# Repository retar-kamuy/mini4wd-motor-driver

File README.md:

# Mini 4WD Motor Driver 開発版

[keimyojizai/mini4wd-motor-driver](https://github.com/keimyojizai/mini4wd-motor-driver) を元に開発している [retar-kamuy のフォーク](https://github.com/retar-kamuy/mini4wd-motor-driver) です。

**販売・量産を目的としない個人の趣味用試作です。基板上の全SMT部品を業者へ実装委託して完成させる設計で、手はんだ後付けを前提にしません。発注枚数は固定せず、故障時の交換や予備を含む複数枚注文を想定します。現在の設計は検証中で、発注に使える状態ではありません。** 正規設計は37部品を全てF.Cu側に配置し、記録済み版ではERC・DRC・未接続・回路図不一致は0件、116パッドのネット照合も一致しました。搭載性は一般的な実現性を評価し、個々のシャーシやカウルへの適合は保証しません。フロントモーターのFM-A/SFMは対象外です。部品・ランド、PCBA用BOM/CPL、業者のファイル・組立条件確認が残っています。完成基板の電流・温度・過渡波形は試作後に確認します。品質基準と現版の変更は[趣味用途の品質レビュー](specs/003-resolve-pcb-drc/verification/hobby-quality-review.md)および[試作版の反映記録](specs/003-resolve-pcb-drc/verification/prototype-design-release.md)を参照してください。

**対応電池の設計要件：単3形NiMH充電池2本／単3形アルカリ乾電池2本の両方。** 両電池に対応する方針で電源・駆動回路を設計しています。対応電圧範囲、起動・低電圧時の動作、モーター負荷および実機動作は検証中です。現時点で両電池での動作確認完了を示すものではありません。

**対応モーターの設計意図：型番で限定しないこと。** 代表負荷と保護範囲を確認します。電池との組合せによる起動・ストール・ブレーキ時の過渡電流と保護の検討は未完了で、未知の全モーターの動作保証を意味しません。

| 内容 | 正本・入口 |
|---|---|
| 現行KiCad設計 | [hardware/kicad/mini4wd-motor-driver](hardware/kicad/mini4wd-motor-driver/) |
| 基板の残課題 | [specs/003-resolve-pcb-drc/tasks.md](specs/003-resolve-pcb-drc/tasks.md) |
| ファームウェア | [firmware/mini4ai_v358](firmware/mini4ai_v358/) |
| Webアプリ | [web/index.html](web/index.html) |
| 利用資料 | [docs](docs/) |
| 開発環境 | [SETUP.md](SETUP.md) |
| 構成と来歴 | [docs/repository_structure.md](docs/repository_structure.md) |

以下は元プロジェクトを基にした利用案内です。掲載された既存基板の写真・動作説明は、開発中のKiCad基板の製造承認を意味しません。

---

# ミニ四駆AI モータードライバ基板

**XIAO MG24 Sense専用 / 正転専用 / ショートブレーキ対応 MOSFETドライバ**

ミニ四駆に電子制御を追加するための、  
**XIAO MG24 Sense専用 高電流モータードライバ基板**です。

- **Nch MOSFETによるモーター駆動**
- **Pch MOSFETによるショートブレーキ**
- **1本のPWM信号で駆動 / 制動を切り替え**
- **発進時のソフトスタートに対応**
- **電池電圧・M-側電圧・基板温度の観測に対応**
- **Ni-MH 2セル / Li-ion 1セル向け**

> 本基板は、改造・競技・研究・教育用途を想定した電子工作向け部品です。  
> はんだ付け、配線、電源極性、モーター制御に関する基礎知識が必要です。

---

## 購入後に使用するもの

本基板を使用するには、XIAO MG24 Senseへ専用ファームウェアを書き込み、WebアプリからBLE接続して設定・走行制御を行います。

- [Webアプリを開く](https://keimyojizai.github.io/mini4wd-motor-driver/)
- [Windows書き込みツールをダウンロード](https://github.com/keimyojizai/mini4wd-motor-driver/releases/latest)
- [ファームウェア更新手順](docs/firmware_update.md)
- [本体へ保存とスタンドアローン起動](docs/standalone_mode.md)
- [Arduino IDEで手動書き込みする手順](docs/flash_arduino_ide.md)
- [書き込みに失敗した場合の復旧手順](docs/recovery.md)

### Webアプリでできること

- デバイスへのBLE接続
- 走行開始・停止
- 認識調整
- ルール設定
- かんたん設定で、90度/180度/それ以上のカーブ継続を別々に選択
- 別画面のかんたん設定ウィザード（1画面1判断）
- かんたん設定内で2つ目・3つ目のルールを追加可能
- かんたん設定中は専用ルールセットだけを走行に反映し、過去ルールとの重複発火を防止
- 目的位置の手前を起点にした時間差アクション設定
- 電圧補正設定
- ラップタイム確認
- 停止後ログ確認
- ヘッダー非表示による走行・ラップ表示の拡大
- ファームウェアバージョン確認
- BLE表示名の変更
- 現在の設定を本体へ保存
- 保存済み設定によるスタンドアローン起動

### 初回ファームウェア書き込み

初回使用時、またはファームウェア更新時は、Windows用書き込みツールを使用してください。

1. GitHub ReleasesからWindows用書き込みツールをダウンロードします。
2. ZIPを右クリックして「すべて展開」します。
3. 展開したフォルダ内の `START_HERE_Flash_Mini4AI.cmd` を実行します。
4. 書き込み時に、BLE表示名を自由に設定できます。

> ファームウェア書き込み時は、**ミニ四駆側の電源をオフ** にしてからUSB接続してください。

macOS / Linux用の書き込みツールは、現時点では動作確認対象外のため同梱していません。Windows用書き込みツールでうまくいかない場合や、他OSで使用する場合はArduino IDEで手動書き込みしてください。

### 本体へ保存とスタンドアローン起動

Webアプリで設定した内容には、**一時適用**と**本体へ保存**があります。

- **走行開始**: 現在の画面設定を一時的に本体へ送信して走行します。電源を切ると、この一時設定は残りません。
- **本体へ保存**: 現在のパラメータ、ルール、電圧補正、周回認識設定をXIAO MG24 Sense本体へ保存します。
- **スタンドアローン起動**: 保存済み設定がある状態で、裏返しのまま電源ON → 表向きに戻す → 約3秒後にBLEなしで自動スタートします。

スタンドアローン起動で使いたい設定は、必ずWebアプリ左メニューの **「本体へ保存」** を押してから使用してください。

Webアプリでは、誤操作を避けるため「走行開始」「停止」とは離した左メニューに **本体へ保存** を配置しています。保存時には確認画面で「はい / いいえ」を選択します。

詳細は [本体へ保存とスタンドアローン起動](docs/standalone_mode.md) を参照してください。

### かんたん設定モード

Webアプリには、通常の詳細UIとは別に、1画面1判断で進む **かんたん設定** があります。
目的位置、起点セクション、発動回数、待機時間、ブレーキ/低出力を順番に設定できます。

走行後に「早すぎた」「遅すぎた」「発動しなかった」「違う場所でも発動した」を選ぶと、修正すべき画面へ戻ります。
このとき、改善アドバイスを画面上部に表示し続けるため、何を直すべきか確認しながら調整できます。

1つ目のルールが決まった後も、かんたん設定のまま2つ目・3つ目のルールを追加できます。

### 推奨バージョン

| 項目 | 推奨バージョン |
|---|---|
| Webアプリ | v4.21-r33 |

かんたん設定では単発の左C/右Cを初期状態で非表示にし、誤発動しにくい左/右カーブ継続を基本にしています。
| ファームウェア | v3.58-r10 |

Webアプリ上で、接続中デバイスのファームウェアバージョンを確認できます。

---

## 外観・パッケージ・装着例

### 基板単体

### 販売パッケージ

### ミニ四駆への装着例

> 装着例です。ミニ四駆車体、XIAO MG24 Sense、モーター、電池、配線材等は付属しません。

### 動作例

[YouTube Shortsで動作例を見る](https://youtube.com/shorts/a6D7kiM3N_Y?feature=share)

---

## どのような基板か

本基板は、ミニ四駆で一般的な

```text
M+ / B+ = 電池＋ / モーター＋ 共通
M-      = モーター−
B-      = 電池−
```

という構成を前提にした、**正転専用・M-側制御**のモータードライバです。

Hブリッジではなく、機能を

- **正転駆動**
- **ショートブレーキ**
- **各種センシング**

に絞ることで、ミニ四駆AI制御向けに小型化と高電流駆動を狙っています。

---

## 主な特徴

- **XIAO MG24 Sense専用設計**
- **正転専用**。逆転制御には非対応
- **Nch MOSFETによる低側駆動**
- **Pch MOSFETによるショートブレーキ**
- **UCC27511による5Vゲート駆動**
- **TPS61023による5V昇圧電源**
- **XIAO MG24 Senseへの5V給電**
- **VBAT / MID / 温度の観測に対応**
- **発進時のソフトスタートに対応**
- **DRV8835系ドライバでは駆動できなかったモーターの駆動を手元評価で確認**

---

## ソフトウェア制御について

本基板は、XIAO MG24 Sense上のファームウェアでモーターを制御します。

- 走行開始時は、設定されたDutyへ一気に上げず、短時間のソフトスタートを行います。
- 走行中のルール判定、ブレーキ、低出力制御は本体側で実行されます。
- Webアプリは、設定・開始/停止指示・ログ確認を行うための操作画面です。
- Webアプリの走行開始は、現在の画面設定を一時適用します。
- スタンドアローン起動で使う設定は、Webアプリの **「本体へ保存」** を押したときだけ更新されます。
- BLE接続が切れても、走行中の制御判断は本体側で継続します。

## ルール設計の基本

目的の場所で止める、または減速する場合は、**その場所そのものを認識してからブレーキするのではなく、手前の特徴的なセクションを起点にして時間差でアクション**します。

例として、ウェーブで止まりたい場合、ウェーブを認識してからブレーキすると遅れることがあります。ウェーブの手前にある特徴的なセクションを起点にし、待機msで位置を合わせてからブレーキ/低出力を出します。

最初は1〜2セグメントの短い条件で作り、同じ起点が複数回出る場合は、奇数回・偶数回・N回のみの発動条件を使います。

Webアプリの **かんたん設定** は通常画面とは別画面で開き、1画面につき1つの判断だけを表示します。
最後の接続前には、設定したルールを自然文で確認できます。
走行後は「発動しない」「早すぎる」「遅すぎる」「余計な場所でも出る」から選ぶと、次に触るべき設定を1つに絞って提案します。

詳細は [かんたん設定ウィザード](docs/guided_setup.md) を参照してください。

---

## 重要な注意事項

使用前に必ず確認してください。

```text
・XIAO MG24 Sense専用です
・XIAO MG24 Senseは付属しません
・正転専用です
・逆転制御はできません
・Hブリッジではありません
・PWM Duty 0%ではショートブレーキになります
・電池の逆接続は禁止です
・Li-ion 2セルは禁止です
・8.4V系電源は禁止です
・FM-A / SFMシャーシには基本的に非対応です
・フェンスカー等の電池逆向き運用には、そのまま使用できません
・ファームウェア書き込み時は、ミニ四駆側の電源をオフにしてからUSB接続してください
```

---

## 基本仕様

| 項目 | 内容 |
|---|---|
| 対応マイコン | XIAO MG24 Sense専用 |
| 駆動方式 | 正転専用、M-側制御 |
| モーター制御 | Nch MOSFET低側駆動 |
| ブレーキ | Pch MOSFETによるショートブレーキ |
| 制御信号 | PWM入力 1本 |
| 想定電源 | Ni-MH 2セル / Li-ion 1セル |
| 非対応電源 | Li-ion 2セル、8.4V系電源 |
| 基板サイズ | 約 55 mm × 21 mm |
| 基板厚 | 1.2 mm |

---

## 接続概要

### 大電流端子

```text
M+ / B+ = 電池＋ / モーター＋ 共通
M-      = モーター−
B-      = 電池−
```

### XIAO MG24 Senseとのピン対応

| XIAO MG24 Sense | 本基板での機能 |
|---|---|
| 5V | 5V OUT |
| GND | GND |
| PC0（D0） | VBAT SENSE |
| PC1（D1） | NTC TEMP |
| PC2（D2） | MOTOR PWM |
| PC3（D3） | MID SENSE |

---

## 詳細ドキュメント

READMEでは概要のみを示しています。  
設計意図・配線・動作原理・注意事項の詳細は、以下を参照してください。

- [ファームウェア更新手順](docs/firmware_update.md)
- [本体へ保存とスタンドアローン起動](docs/standalone_mode.md)
- [Arduino IDEで手動書き込みする手順](docs/flash_arduino_ide.md)
- [書き込みに失敗した場合の復旧手順](docs/recovery.md)
- [トラブルシュート](docs/troubleshooting.md)
- [かんたん設定ウィザード](docs/guided_setup.md)
- [ハードウェア仕様と主要部品](docs/hardware_spec.md)
- [配線・取り付け・対応シャーシ](docs/wiring_and_usage.md)
- [PWM制御とショートブレーキの動作](docs/pwm_and_brake.md)
- [安全上の注意・免責事項・サポート](docs/safety_and_support.md)

---

## サポート

不具合報告・質問・改善提案は、GitHubの **Issues** を使用してください。  
問い合わせ時は、以下の情報を記載してください。

- 使用しているWebアプリのバージョン
- 使用しているファームウェアのバージョン
- XIAO MG24 SenseのBLE表示名
- 使用電源
- 使用モーター
- 症状が起きた操作手順
- 可能であれば、Webアプリの停止後ログ

---

## 商標について

- ミニ四駆は株式会社タミヤの登録商標です。
- 本基板は株式会社タミヤの公式製品・公認製品ではありません。
- 本基板は個人開発の改造・実験用基板です。

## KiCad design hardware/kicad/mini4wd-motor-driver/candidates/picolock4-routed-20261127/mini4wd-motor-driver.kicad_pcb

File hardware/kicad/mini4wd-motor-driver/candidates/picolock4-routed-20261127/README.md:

# 004 Pico-Lock 4極・配線候補

2026-11-27。4極コネクタ案の別候補。004正規版と元の `picolock4-20261126` は変更していない。J1を右へ5 mm移動、右端を5.5 mm延長し、外形は60.5 × 21 mmとなった。元の55 × 21 mmに対する車体収納は未確認。

J1のピン1=MOTOR_MINUS、2=VBAT（モーター＋）、3=GND（電池−）、4=VBAT（電池＋）。電池とモーターを1つにまとめる専用ハーネスが必要。極性を回路図とメーカー図面で再確認する。旧配置のB+/B−/M+/M−シルクはF.Fabに移動し、ピンの位置に対応する新しい表示を表面シルクへ追加した。J1の基板端からはみ出すシルク外形もF.Fabへ移した。

旧候補のJ1付近の配線を整理し、自動配線で再接続した。新規配線はVBAT/MOTOR_MINUS/GNDに1.0 mmの指定を与えたが、電流経路には既存の細線やビアも含まれる。1.0 mm指定やDRC合格は5 A連続の許容を意味せず、電流分流、銅厚、ビア、発熱は未評価。メーカーの4極AWG20参考値は5.5 A/極で、始動・拘束の適否も未確定。[Molex仕様](https://www.molex.com/content/dam/molex/molex-dot-com/en_us/pdf/datasheets/987650-9061.pdf)

2026-11-28、J1の電池マイナスから裏面GND面への接続が1本のビアに集中していたため、元の1本に加え穴径0.3 mmのビアを3本並列に追加した。追加後のDRC・未接続・パリティは0件。配線の電流分流・熱容量・実装後の温度は未検証であり、5 A連続を保証しない。裏面はGND銅箔面とビアを使用するため、電池との接触防止に絶縁材と機械的保持が必要。

KiCad 10.0.8で `erc-final.json`: ERC 0件、`drc-final.json`: DRC 0件・未接続0件・回路図パリティ0件。旧コピーの `drc.json`、`drc-20261127.json`、`erc.json` は変更前の履歴である。レイヤー数・回路の詳細検査、コネクタのハーネス・電流熱・Seeed Fusion部品調達・車体寸法は別途必要。

`3d-preview.png` はユーザー提供の `2053380004.stp` をJ1に設定した表示。KiCadのモデルオフセットは (3, -8.09, 0.06) mm、回転0°。3D描画上の端子とパッドの位置を目視で照合した。相手側ハウジング・ケーブルは描画しておらず、車体との干渉や抜き差し余地は未確認。以前の直方体 `J1_PICOLOCK_ENVELOPE_APPROX.step` は参考として残し、使用していない。

**発注・通電用には未完成。** ERC/DRCだけでは高電流、電池・車体への収納、EMC、部品調達や実装可否を保証しない。

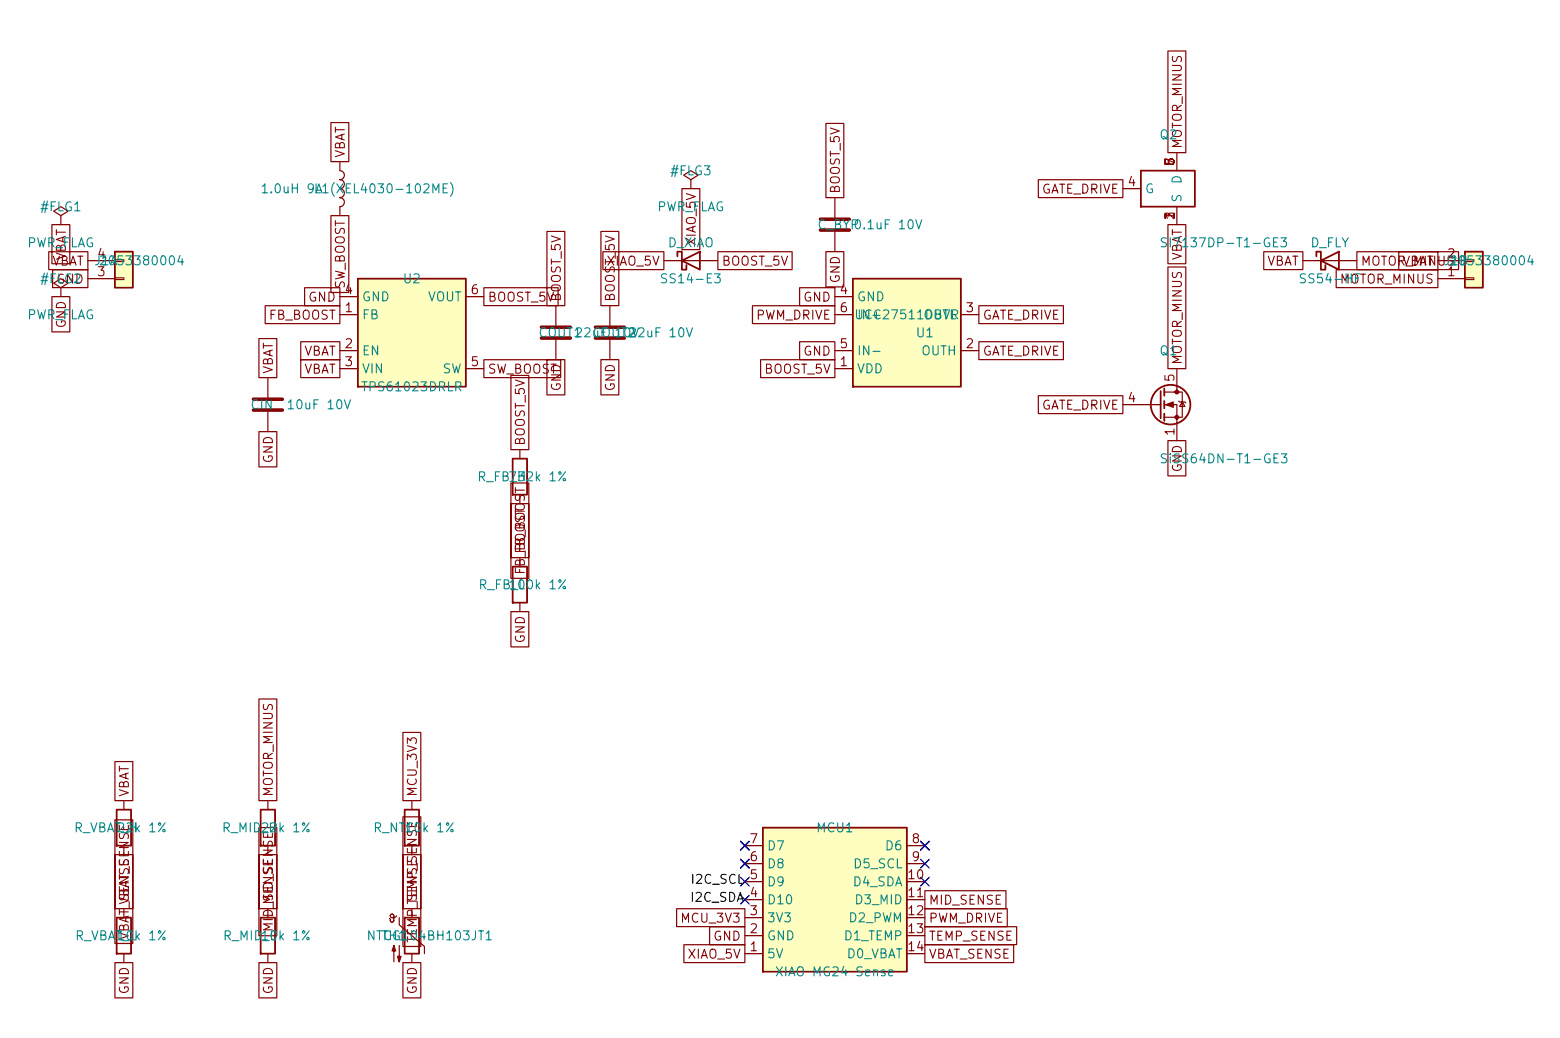
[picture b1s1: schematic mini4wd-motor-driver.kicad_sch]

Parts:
CIN: 10uF 10V; C_0603_1608Metric
COUT1, COUT2: 22uF 10V; C_0603_1608Metric
C_BYP: 0.1uF 10V; C_0402_1005Metric
D_FLY: SS54-HF; D_SMA
D_XIAO: SS14-E3; D_SMA
J1: 2053380004; Molex_Pico-Lock_205338-0004_1x04-1MP_P2.00mm_Horizontal
L1: 1.0uH 9A (XEL4030-102ME); Coilcraft_XEL4030
MCU1: XIAO MG24 Sense; XIAO_MG24_Castellated_14P
Q1: SiSS64DN-T1-GE3; Vishay_PowerPAK_1212-8_Single
Q2: SI7137DP-T1-GE3; PowerPAK_SO-8_SI7137DP
R_FB_H: 732k 1%; R_0603_1608Metric
R_FB_L: 100k 1%; R_0603_1608Metric
R_MID_H: 22k 1%; R_0603_1608Metric
R_MID_L: 10k 1%; R_0603_1608Metric
R_NTC: 10k 1%; R_0603_1608Metric
R_VBAT_H: 22k 1%; R_0603_1608Metric
R_VBAT_L: 10k 1%; R_0603_1608Metric
TH1: NTCG104BH103JT1; R_0402_1005Metric
U1: UCC27511DBVR; SOT-23-6
U2: TPS61023DRLR; Texas_R-PDSO-N6_DRL-6

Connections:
/I2C_SCL: MCU1.5 (D9)
/I2C_SDA: MCU1.4 (D10)
BOOST_5V: COUT1.1, COUT2.1, C_BYP.1, D_XIAO.2 (A), R_FB_H.1, U1.1 (VDD), U2.6 (VOUT)
FB_BOOST: R_FB_H.2, R_FB_L.1, U2.1 (FB)
GATE_DRIVE: Q1.4 (G), Q2.4 (G), U1.2 (OUTH), U1.3 (OUTL)
GND: CIN.2, COUT1.2, COUT2.2, C_BYP.2, J1.3 (B-), MCU1.2 (GND), Q1.1 (S), Q1.2 (S), Q1.3 (S), R_FB_L.2, R_MID_L.2, R_VBAT_L.2, TH1.2, U1.4 (GND), U1.5 (IN-), U2.4 (GND)
MCU_3V3: MCU1.3 (3V3), R_NTC.1
MID_SENSE: MCU1.11 (D3_MID), R_MID_H.2, R_MID_L.1
MOTOR_MINUS: D_FLY.2 (A), J1.1 (M-), Q1.5 (D), Q2.5 (D), Q2.6 (D), Q2.7 (D), Q2.8 (D), R_MID_H.1
PWM_DRIVE: MCU1.12 (D2_PWM), U1.6 (IN+)
SW_BOOST: L1.2, U2.5 (SW)
TEMP_SENSE: MCU1.13 (D1_TEMP), R_NTC.2, TH1.1
VBAT: CIN.1, D_FLY.1 (K), J1.2 (M+), J1.4 (B+), L1.1, Q2.1 (S), Q2.2 (S), Q2.3 (S), R_VBAT_H.1, U2.2 (EN), U2.3 (VIN)
VBAT_SENSE: MCU1.14 (D0_VBAT), R_VBAT_H.2, R_VBAT_L.1
XIAO_5V: D_XIAO.1 (K), MCU1.1 (5V)

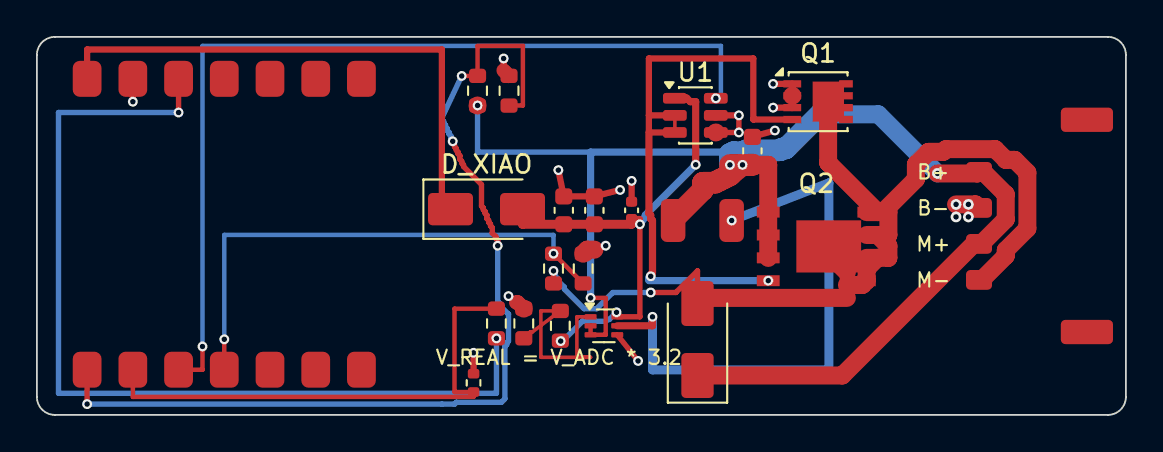
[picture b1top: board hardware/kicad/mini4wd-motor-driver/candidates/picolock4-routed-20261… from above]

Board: 2 copper layers, 60.5 x 21.0 mm, 21 parts (0 on the bottom side), 13 nets.

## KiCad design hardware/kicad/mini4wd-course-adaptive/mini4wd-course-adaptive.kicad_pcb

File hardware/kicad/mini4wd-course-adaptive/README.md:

# 006 車載ブラシレス制御 PCB 初版候補

2026-11-22。正本は `mini4wd-course-adaptive.kicad_sch` と同名プロジェクトです。市販シャーシの四輪駆動を残し、MCT8316ZRでHall付きROCKET-RC MINI 1525 5500KVを電流制限付きで評価する初版設計。XIAO MG24 SenseのBLE、車載IMU、内蔵メモリーを使います。初版の速度、実機温度、VZへの収まりは実測前です。

## 接続と電源

| 接続 | PCB側の割り当て | 条件 |
|---|---|---|
| J1 | 1: BAT_RAW、2: GND | Micro-Fit 3.0の極性を合わせた外部ヒューズ付き配線。2S候補。VBpower標準PHを大電流の出力経路として扱わない。 |
| J2 | 1: PH_A、2: PH_B、3: PH_C | 基板への直接はんだ付け用電線穴。0.25 mm²のフットプリントを選択。モーター線と相順の確定後に接続する。ワイヤは保持・絶縁する。 |
| J3 | 1: HALL_VCC、2: GND、3: A入力、4: B入力、5: C入力 | PCB側の順序。1525の5ピンへ直接差し込む仕様ではない。変換ハーネスで極性・相順・レベルを合わせる。 |
| J4 | 1: MCU_3V3、2: WHEEL、3: GND | 3.3 V対応の外部車輪センサー。ボード側10 kΩプルアップあり。 |
| TP1〜4 | DRVOFF、ILIM、AVDD、GND | 初回通電の測定点。 |

AP63205系の5 VをXIAOの5V端子へSchottky経由で供給。Schottkyはレギュレーターへの逆流を制限する。USBからモーター母線を給電しない。USB接続時はバッテリーを物理的に外す。初回電源はバッテリーとホットプラグを避け、電流・立ち上がり速度を制限した電源を使う。U1のVM立ち上がり絶対最大は4 V/µs。D1で母線過渡の抑制を意図するが、TVSの公称値をモーター端子の8.4 V制限とみなさない。[MCT8316Z Rev.B §7・§9・§11](https://www.ti.com/lit/ds/symlink/mct8316z.pdf)・[AP63205 データシート](https://www.diodes.com/datasheet/download/AP63200-AP63201-AP63203-AP63205.pdf)

Hall入力はU3でAVDDレベルに変換し、U1はデジタルHallモードで使用予定。HNxは開放。R12（AVDD）・R13（5 V）両方DNPで、モーター型番のセンサー給電条件を確定してから片方だけ取り付ける。R14〜R16もDNPで、出力形式を確認した際にのみ取り付ける。AVDDから給電する総負荷はU3/U5等の負荷を含めMCTの30 mA上限内とする。メーカーの端子配列・電圧・出力形式・位相対応は未取得。[MCT8316Z Rev.B §6・§8.3.2](https://www.ti.com/lit/ds/symlink/mct8316z.pdf)・[SN74LVC125A](https://www.ti.com/lit/ds/symlink/sn74lvc125a.pdf)

## MCU端子

| MCU | ネット | 機能 |
|---|---|---|
| D0 | VBAT_SENSE | 分圧240 kΩ/100 kΩ。VM 8.4 V時の公称2.47 V。ADC取得時間・校正と無給電時の注入電流を確認。 |
| D1 | WDI | 外部watchdog。制御ループ健全時に立下りを発行。 |
| D2 | MCU_PWM | U5経由で速度PWM。起動はLow。 |
| D3 | MCU_NCS | SPI選択。起動はHigh。 |
| D4 | ARM_EDGE | 出力禁止の解除には新しい立上りを要求。 |
| D5 | MCU_NFAULT | U6経由の故障読取。停止中のnFAULT状態もSPIと照合。 |
| D6 | WHEEL | 車輪パルス。 |
| D7 | HOST_RUN | 許可High。Lowおよびリセット時はラッチの非同期解除（禁止側）。 |
| D8 / D9 / D10 | MCU_SCK / MCU_MISO / MCU_MOSI | U5/U6を経由したMCTのSPI。 |
| 底面・内蔵用信号 | モジュール内 | 内蔵IMU/Flash接続を外部用途に割り当てない。 |

モジュール専用のパッド番号は003の既存ランドに合わせた番号です。D0=ランド14、D10=ランド4、5V=ランド1。MCU GPIO番号と同じ番号ではありません。[Seeed MG24 Sense端子表](https://wiki.seeedstudio.com/xiao_mg24_getting_started/)

## 禁止側の初期状態と通電順

1. R28（ARM LINK）をDNPにした状態で受領・実装検査する。U1 DRVOFFはAVDD側のR7でHighに保つ。BRAKEはLow固定。Q2は両方の電源が有効で、かつハードウェアラッチに許可が入った後にだけDRVOFFを引き下げる設計。R28未実装ではQ2をR29がOFFに保つ。
2. モーターとHallハーネスを外し、電流制限付き電源でAVDD、ロジック電源、DRVOFF、三相のHi-Zを確認する。DRVOFF Lowを駆動停止と取り違えない。USB・入力の片側給電、再投入を別々に確認する。
3. U7はTPS3431固定時間モード（SET1 High、CWDから10 kΩをVDD）。WDO/ENOUTはオープンドレインとして論理積を構成。U8が `WD_OK AND HOST_RUN` をラッチのnCLRへ出す。時計エッジのない通信復帰ではQは自動で許可にならない。タイムアウト時間、電圧復帰時、終了順は実測する。
4. 真のモーター端子表、相抵抗・相インダクタンスと入力上限を取得し、適合する変換ハーネスを作る。PWM=0の状態でSPI構成を書き込み、読戻しを照合する。MCTはモードにより111をアラインメントに使えるため、不正Hall状態での停止も確認する。
5. R5/R6 11.0 kΩ/10.0 kΩのILIM設定はAVDD=3.3 V、CSA=0.15 V/Aで約1.57 Aの計算点。パルスのブランキング、巻線インダクタンス、許容差、熱により実ピークは変わる。許可リンクを入れる前に回路側の禁止動作を確認し、リンク装着後の初回駆動も電流を制限して相電流を計測する。

回路図上の電流や遮断条件は設計値です。走行用の閾値・温度上限・停止時間を保証するものではありません。PCBの電力配線、RF近傍の銅箔、JLCPCBの部品受入・向き、シャーシ実寸は発注資料の確定時に確認します。

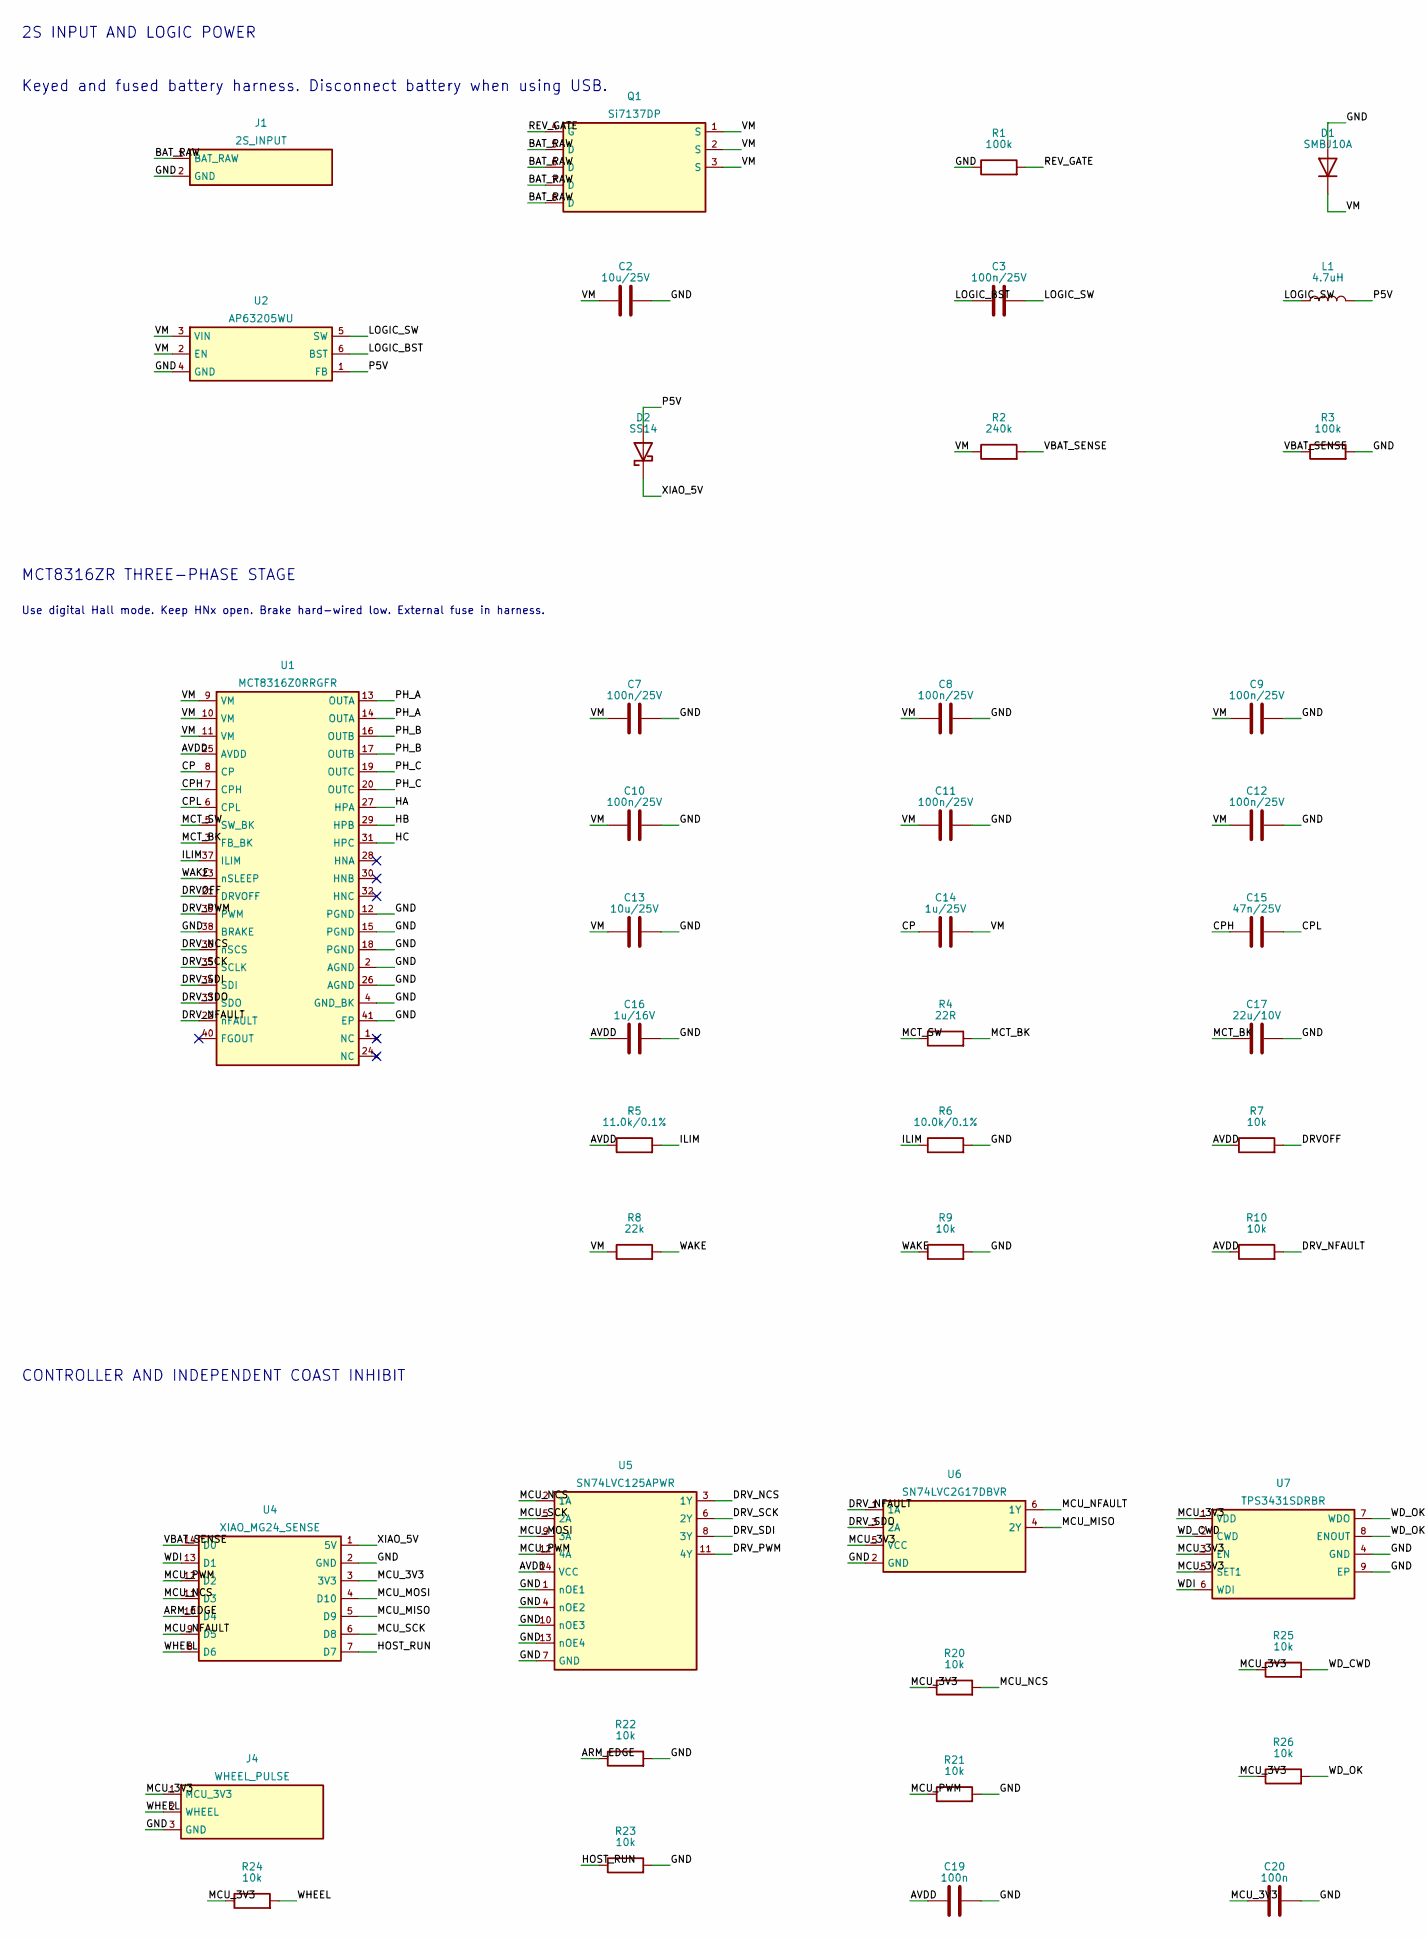
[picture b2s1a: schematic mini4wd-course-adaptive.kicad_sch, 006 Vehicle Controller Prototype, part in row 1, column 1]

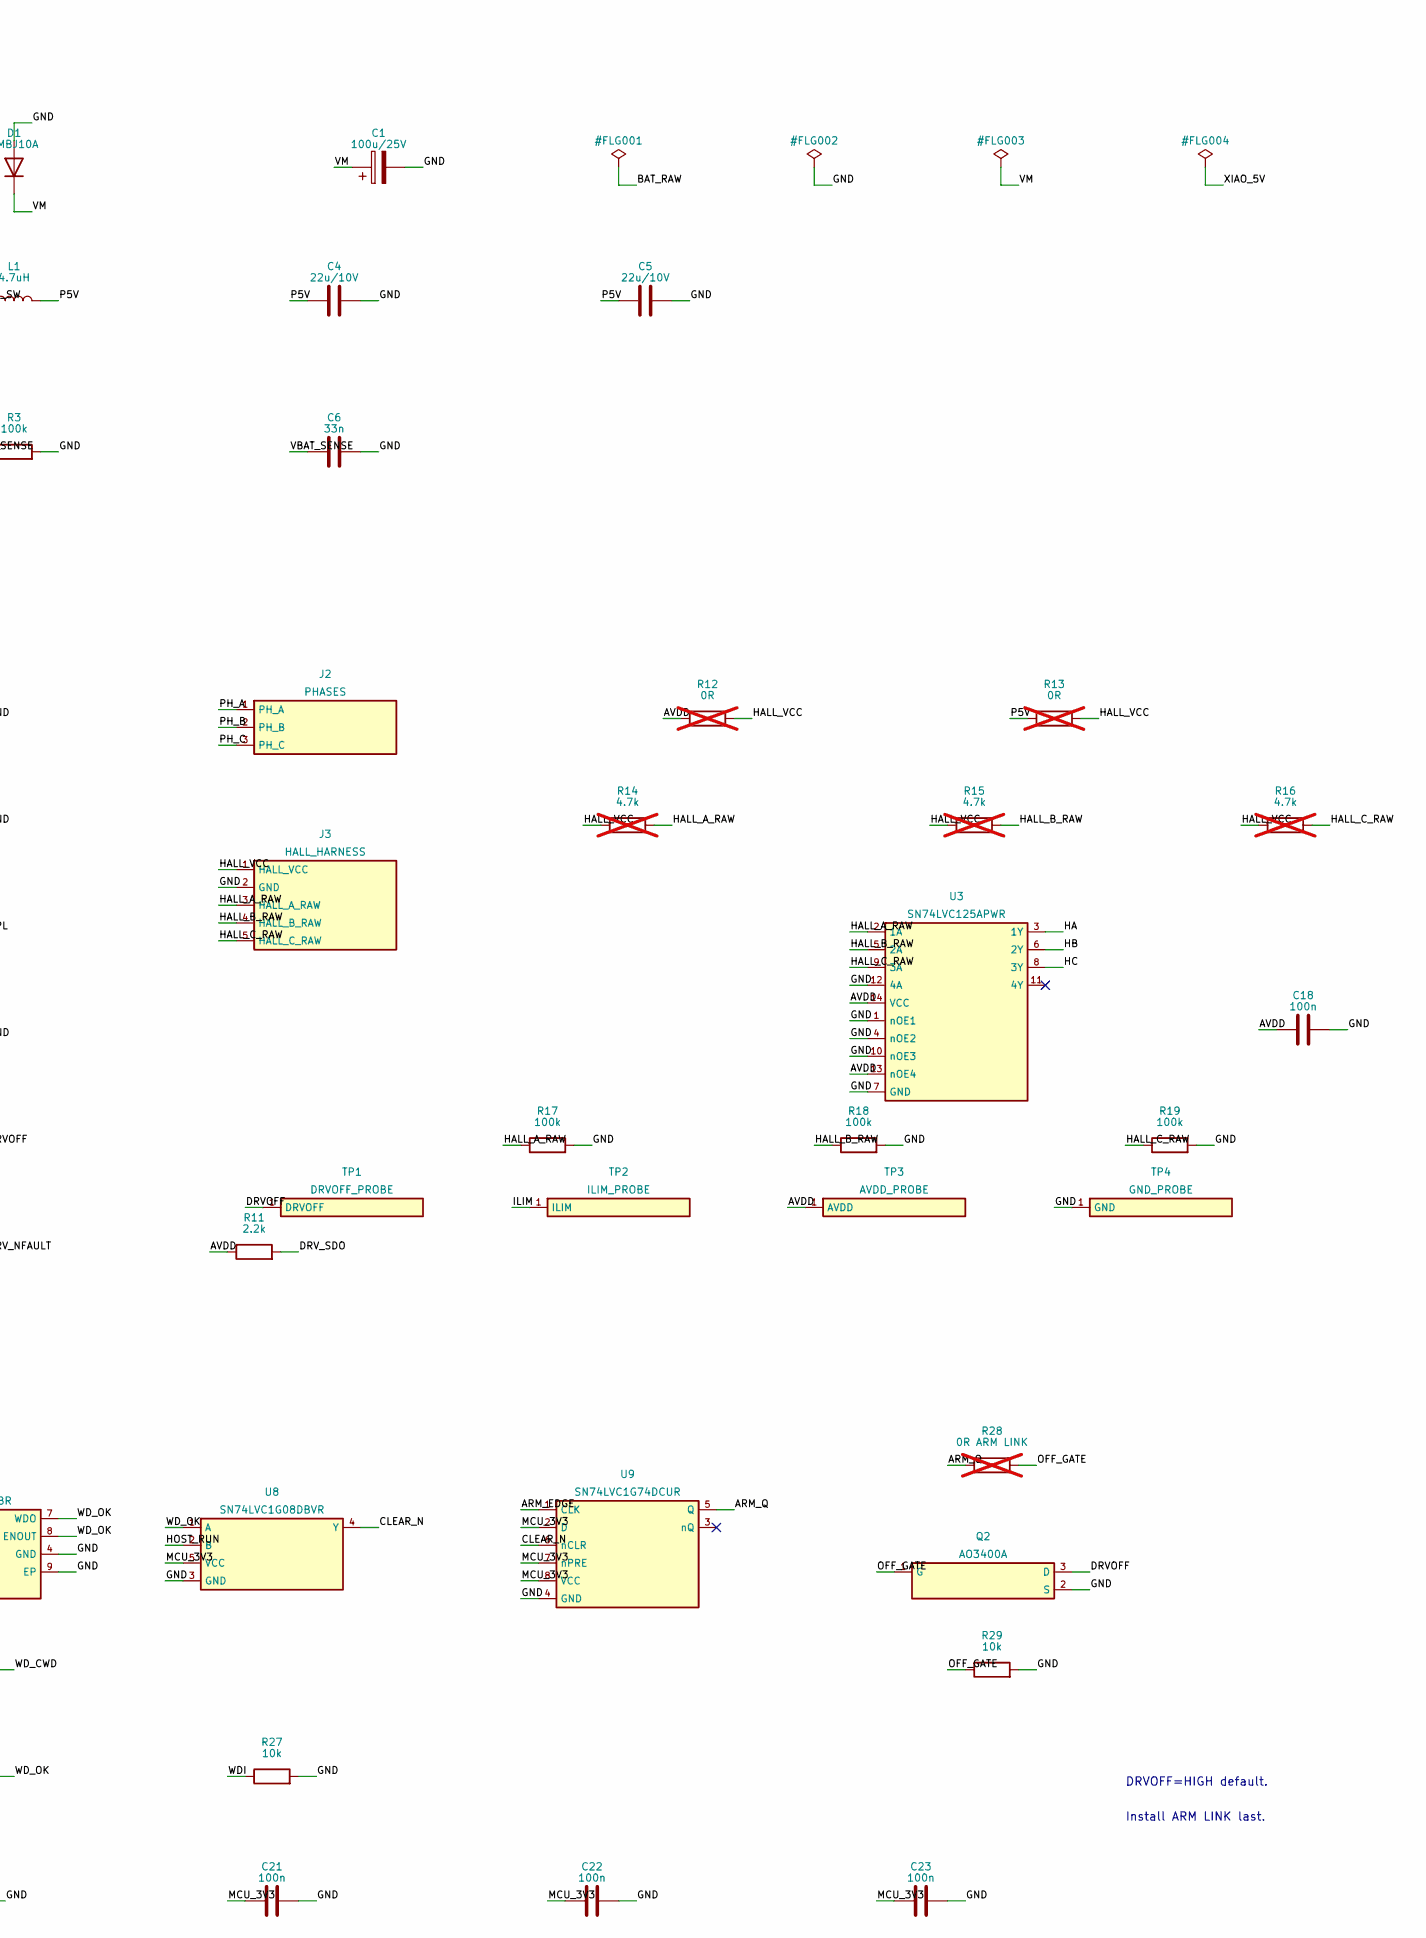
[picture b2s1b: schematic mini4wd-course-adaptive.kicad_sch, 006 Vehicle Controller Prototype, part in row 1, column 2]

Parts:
C1: 100u/25V; CP_Elec_6.3x7.7
C2, C13: 10u/25V; C_0805_2012Metric
C3, C7, C8, C9, C10, C11, C12: 100n/25V; C_0603_1608Metric
C4, C5, C17: 22u/10V; C_0805_2012Metric
C6: 33n; C_0603_1608Metric
C14: 1u/25V; C_0603_1608Metric
C15: 47n/25V; C_0603_1608Metric
C16: 1u/16V; C_0603_1608Metric
C18, C19, C20, C21, C22, C23: 100n; C_0603_1608Metric
D1: SMBJ10A; D_SMB; MPN SMBJ10A
D2: SS14; D_SMA; MPN SS14-E3/61T
J1: 2S_INPUT; Molex_Micro-Fit_3.0_43045-0200_2x01_P3.00mm_Horizontal; MPN 43045-0200
J2: PHASES; SolderWire-0.25sqmm_1x03_P4.5mm_D0.65mm_OD2mm
J3: HALL_HARNESS; JST_PH_B5B-PH-K_1x05_P2.00mm_Vertical; MPN B5B-PH-K-S(LF)(SN)
J4: WHEEL_PULSE; JST_PH_B3B-PH-K_1x03_P2.00mm_Vertical; MPN B3B-PH-K-S(LF)(SN)
L1: 4.7uH; L_Coilcraft_XAL4030-XXX; MPN XAL4030-472MEB
Q1: Si7137DP; PowerPAK_SO-8_SI7137DP; MPN SI7137DP-T1-GE3; LCSC C784367
Q2: AO3400A; SOT-23; MPN AO3400A; LCSC C20917
R1, R3, R17, R18, R19: 100k; R_0603_1608Metric
R2: 240k; R_0603_1608Metric
R4: 22R; R_0805_2012Metric
R5: 11.0k/0.1%; R_0603_1608Metric; MPN RT0603BRD0711KL
R6: 10.0k/0.1%; R_0603_1608Metric; MPN RT0603BRD0710KL
R7, R9, R10, R20, R21, R22, R23, R24, R25, R26, R27, R29: 10k; R_0603_1608Metric
R8: 22k; R_0603_1608Metric
R11: 2.2k; R_0603_1608Metric
R12, R13: 0R; R_0603_1608Metric; not fitted
R14, R15, R16: 4.7k; R_0603_1608Metric; not fitted
R28: 0R ARM LINK; R_0603_1608Metric; not fitted
TP1: DRVOFF_PROBE; TestPoint_Pad_D1.5mm
TP2: ILIM_PROBE; TestPoint_Pad_D1.5mm
TP3: AVDD_PROBE; TestPoint_Pad_D1.5mm
TP4: GND_PROBE; TestPoint_Pad_D1.5mm
U1: MCT8316Z0RRGFR; TI_RGF0040E_VQFN-40_EP; MPN MCT8316Z0RRGFR; LCSC C3681249
U2: AP63205WU; TSOT-23-6; MPN AP63205WU-7; LCSC C2071056
U3, U5: SN74LVC125APWR; TSSOP-14_4.4x5mm_P0.65mm; MPN SN74LVC125APWR; LCSC C7813
U4: XIAO_MG24_SENSE; XIAO_MG24_Castellated_14P; MPN 102010610; LCSC C43343258
U6: SN74LVC2G17DBVR; SOT-23-6; MPN SN74LVC2G17DBVR; LCSC C10429
U7: TPS3431SDRBR; VSON-8-1EP_3x3mm_P0.65mm_EP1.65x2.4mm; MPN TPS3431SDRBR; LCSC C702145
U8: SN74LVC1G08DBVR; SOT-23-5; MPN SN74LVC1G08DBVR; LCSC C7666
U9: SN74LVC1G74DCUR; VSSOP-8_2.3x2mm_P0.5mm; MPN SN74LVC1G74DCUR; LCSC C70285

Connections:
/ARM_EDGE: R22.1, U4.10 (D4), U9.1 (CLK)
/ARM_Q: R28.1, U9.5 (Q)
/AVDD: C16.1, C18.1, C19.1, R5.1, R7.1, R10.1, R11.1, R12.1, TP3.1 (AVDD_1), U1.25 (AVDD), U3.13 (nOE4), U3.14 (VCC), U5.14 (VCC)
/BAT_RAW: J1.1 (BAT_RAW), Q1.5 (D), Q1.6 (D), Q1.7 (D), Q1.8 (D)
/CLEAR_N: U8.4 (Y), U9.6 (nCLR)
/CP: C14.1, U1.8 (CP)
/CPH: C15.1, U1.7 (CPH)
/CPL: C15.2, U1.6 (CPL)
/DRVOFF: Q2.3 (D), R7.2, TP1.1 (DRVOFF_1), U1.21 (DRVOFF)
/DRV_NCS: U1.36 (nSCS), U5.3 (1Y)
/DRV_NFAULT: R10.2, U1.22 (nFAULT), U6.1 (1A)
/DRV_PWM: U1.39 (PWM), U5.11 (4Y)
/DRV_SCK: U1.35 (SCLK), U5.6 (2Y)
/DRV_SDI: U1.34 (SDI), U5.8 (3Y)
/DRV_SDO: R11.2, U1.33 (SDO), U6.3 (2A)
/GND: C1.2, C2.2, C4.2, C5.2, C6.2, C7.2, C8.2, C9.2, C10.2, C11.2, C12.2, C13.2, C16.2, C17.2, C18.2, C19.2, C20.2, C21.2, C22.2, C23.2, D1.2 (A), J1.2 (GND), J3.2 (GND), J4.3 (GND), Q2.2 (S), R1.1, R3.2, R6.2, R9.2, R17.2, R18.2, R19.2, R21.2, R22.2, R23.2, R27.2, R29.2, TP4.1 (GND_1), U1.2 (AGND), U1.4 (GND_BK), U1.12 (PGND), U1.15 (PGND), U1.18 (PGND), U1.26 (AGND), U1.38 (BRAKE), U1.41 (EP), U2.4 (GND), U3.1 (nOE1), U3.4 (nOE2), U3.7 (GND), U3.10 (nOE3), U3.12 (4A), U4.2 (GND), U5.1 (nOE1), U5.4 (nOE2), U5.7 (GND), U5.10 (nOE3), U5.13 (nOE4), U6.2 (GND), U7.4 (GND), U7.9 (EP), U8.3 (GND), U9.4 (GND)
/HA: U1.27 (HPA), U3.3 (1Y)
/HALL_A_RAW: J3.3 (HALL_A_RAW), R14.2, R17.1, U3.2 (1A)
/HALL_B_RAW: J3.4 (HALL_B_RAW), R15.2, R18.1, U3.5 (2A)
/HALL_C_RAW: J3.5 (HALL_C_RAW), R16.2, R19.1, U3.9 (3A)
/HALL_VCC: J3.1 (HALL_VCC), R12.2, R13.2, R14.1, R15.1, R16.1
/HB: U1.29 (HPB), U3.6 (2Y)
/HC: U1.31 (HPC), U3.8 (3Y)
/HOST_RUN: R23.1, U4.7 (D7), U8.2 (B)
/ILIM: R5.2, R6.1, TP2.1 (ILIM_1), U1.37 (ILIM)
/LOGIC_BST: C3.1, U2.6 (BST)
/LOGIC_SW: C3.2, L1.1, U2.5 (SW)
/MCT_BK: C17.1, R4.2, U1.3 (FB_BK)
/MCT_SW: R4.1, U1.5 (SW_BK)
/MCU_3V3: C20.1, C21.1, C22.1, C23.1, J4.1 (MCU_3V3), R20.1, R24.1, R25.1, R26.1, U4.3 (3V3), U6.5 (VCC), U7.1 (VDD), U7.3 (EN), U7.5 (SET1), U8.5 (VCC), U9.2 (D), U9.7 (nPRE), U9.8 (VCC)
/MCU_MISO: U4.5 (D9), U6.4 (2Y)
/MCU_MOSI: U4.4 (D10), U5.9 (3A)
/MCU_NCS: R20.2, U4.11 (D3), U5.2 (1A)
/MCU_NFAULT: U4.9 (D5), U6.6 (1Y)
/MCU_PWM: R21.1, U4.12 (D2), U5.12 (4A)
/MCU_SCK: U4.6 (D8), U5.5 (2A)
/OFF_GATE: Q2.1 (G), R28.2, R29.1
/P5V: C4.1, C5.1, D2.2 (A), L1.2, R13.1, U2.1 (FB)
/PH_A: J2.1 (PH_A), U1.13 (OUTA), U1.14 (OUTA)
/PH_B: J2.2 (PH_B), U1.16 (OUTB), U1.17 (OUTB)
/PH_C: J2.3 (PH_C), U1.19 (OUTC), U1.20 (OUTC)
/REV_GATE: Q1.4 (G), R1.2
/VBAT_SENSE: C6.1, R2.2, R3.1, U4.14 (D0)
/VM: C1.1, C2.1, C7.1, C8.1, C9.1, C10.1, C11.1, C12.1, C13.1, C14.2, D1.1 (K), Q1.1 (S), Q1.2 (S), Q1.3 (S), R2.1, R8.1, U1.9 (VM), U1.10 (VM), U1.11 (VM), U2.2 (EN), U2.3 (VIN)
/WAKE: R8.2, R9.1, U1.23 (nSLEEP)
/WDI: R27.1, U4.13 (D1), U7.6 (WDI)
/WD_CWD: R25.2, U7.2 (CWD)
/WD_OK: R26.2, U7.7 (WDO), U7.8 (ENOUT), U8.1 (A)
/WHEEL: J4.2 (WHEEL), R24.2, U4.8 (D6)
/XIAO_5V: D2.1 (K), U4.1 (5V)

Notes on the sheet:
2S INPUT AND LOGIC POWER
Keyed and fused battery harness. Disconnect battery when using USB.
MCT8316ZR THREE-PHASE STAGE
Use digital Hall mode. Keep HNx open. Brake hard-wired low. External fuse in harness.
CONTROLLER AND INDEPENDENT COAST INHIBIT
DRVOFF=HIGH default.
Install ARM LINK last.

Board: 4 copper layers, 74 parts (0 on the bottom side), 50 nets, no tracks yet.

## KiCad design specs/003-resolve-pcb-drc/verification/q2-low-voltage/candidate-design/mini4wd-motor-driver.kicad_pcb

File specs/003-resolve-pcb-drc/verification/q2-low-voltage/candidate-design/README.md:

# DMP2008UFG-7 検証候補

正規設計ではありません。発注には使わないでください。正規設計は hardware/kicad/mini4wd-motor-driver/ です。

2026-11-15に正規設計から作成し、Q2を交換、Source/Drain局所配線と小電流VBAT分岐を更新しました。全品F.Cu実装、55×21mm、2銅層、1.6mmを維持します。部品供給・熱・実電源過渡の条件は ../ と ../../q2-low-voltage-review.md を参照。

このコピーには正規設計の他の未確定部品・課題も残っています。検証済みの完成品として扱わないでください。

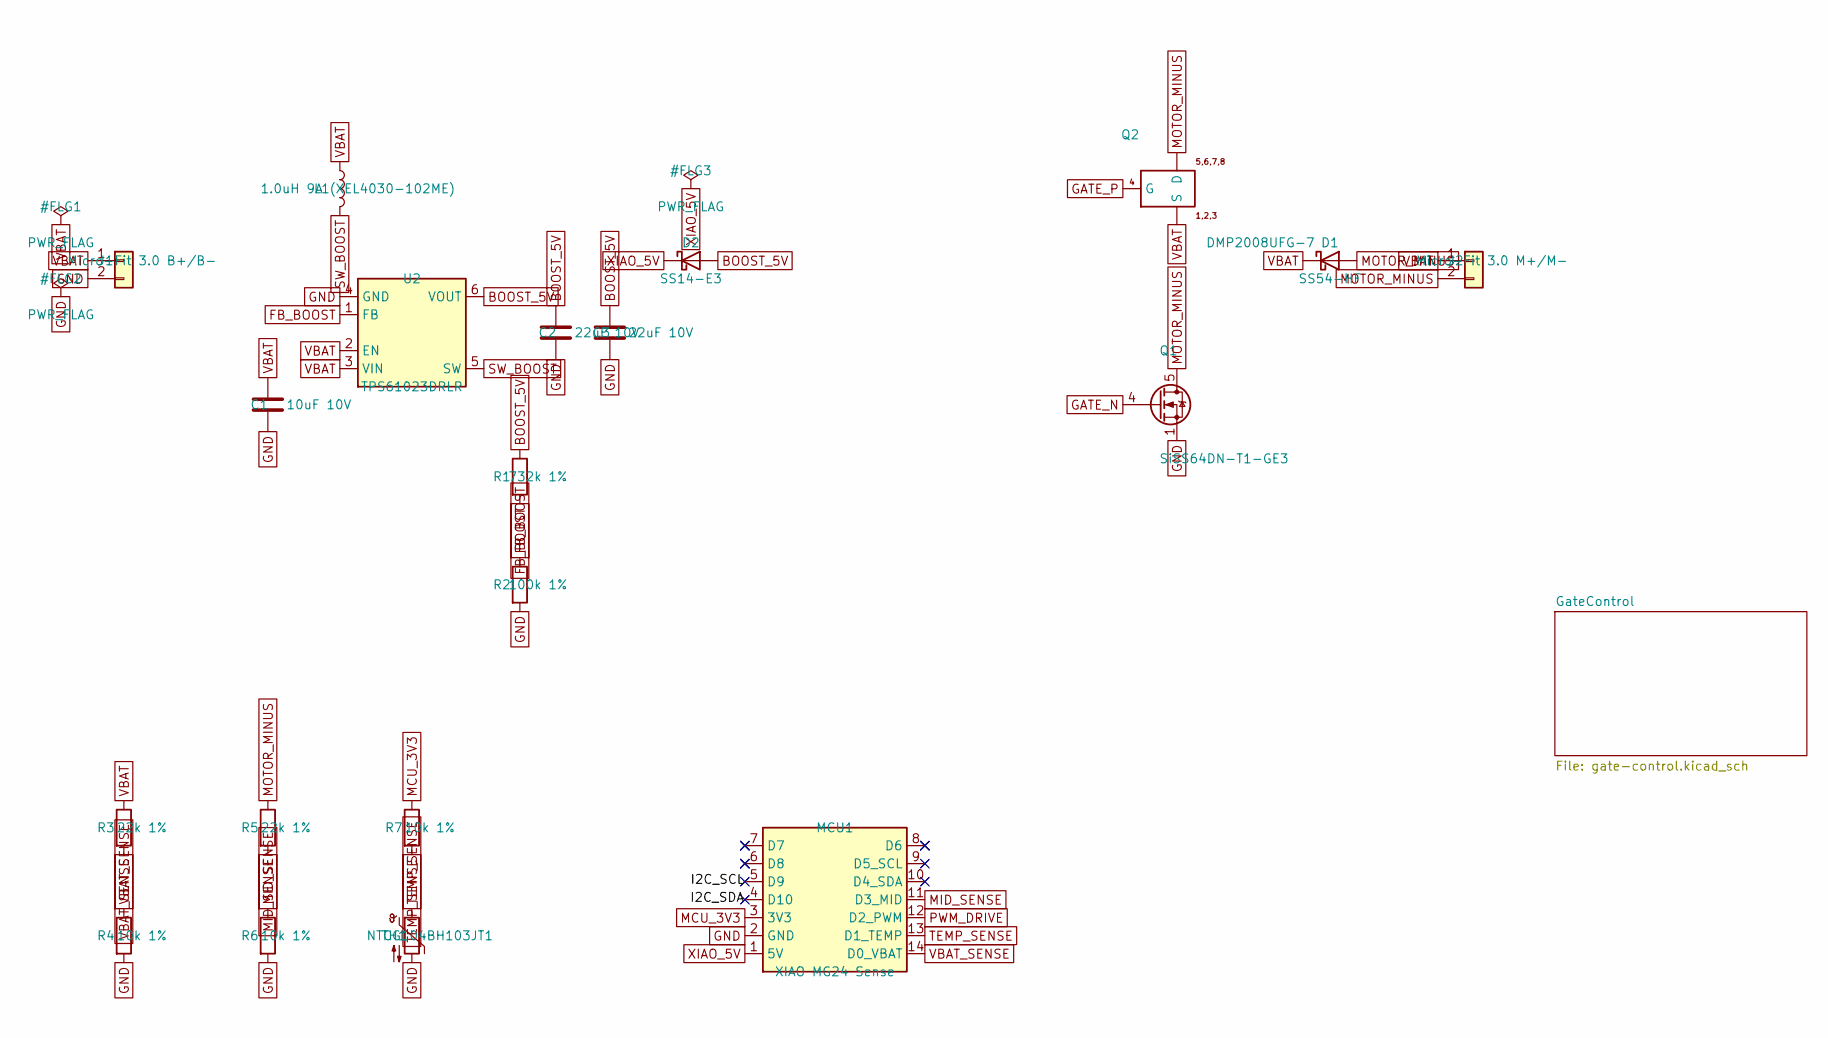
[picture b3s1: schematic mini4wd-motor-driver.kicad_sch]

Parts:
C1: 10uF 10V; C_0603_1608Metric
C2, C3: 22uF 10V; C_0603_1608Metric
D1: SS54-HF; D_SMA
D2: SS14-E3; D_SMA
J1: Micro-Fit 3.0 B+/B-; Molex_MicroFit30_43650-0214
J2: Micro-Fit 3.0 M+/M-; Molex_MicroFit30_43650-0214
L1: 1.0uH 9A (XEL4030-102ME); Coilcraft_XEL4030
MCU1: XIAO MG24 Sense; XIAO_MG24_Castellated_14P
Q1: SiSS64DN-T1-GE3; Vishay_PowerPAK_1212-8_Single; MPN SiSS64DN-T1-GE3
Q2: DMP2008UFG-7; Diodes_PowerDI3333-8_DMP2008UFG; MPN DMP2008UFG-7
R1: 732k 1%; R_0603_1608Metric
R2: 100k 1%; R_0603_1608Metric
R3, R5: 22k 1%; R_0603_1608Metric
R4, R6, R7: 10k 1%; R_0603_1608Metric
TH1: NTCG104BH103JT1; R_0402_1005Metric
U2: TPS61023DRLR; Texas_R-PDSO-N6_DRL-6; MPN TPS61023DRLR

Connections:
/I2C_SCL: MCU1.5 (D9)
/I2C_SDA: MCU1.4 (D10)
BOOST_5V: C2.1, C3.1, D2.2 (A), R1.1, U2.6 (VOUT); also elsewhere on the board
FB_BOOST: R1.2, R2.1, U2.1 (FB)
GATE_N: Q1.4 (G); also elsewhere on the board
GATE_P: Q2.4 (G); also elsewhere on the board
GND: C1.2, C2.2, C3.2, J1.2, MCU1.2 (GND), Q1.1 (S), Q1.2 (S), Q1.3 (S), R2.2, R4.2, R6.2, TH1.2, U2.4 (GND); also elsewhere on the board
MCU_3V3: MCU1.3 (3V3), R7.1; also elsewhere on the board
MID_SENSE: MCU1.11 (D3_MID), R5.2, R6.1
MOTOR_MINUS: D1.2 (A), J2.2, Q1.5 (D), Q2.5 (D), Q2.6 (D), Q2.7 (D), Q2.8 (D), R5.1
PWM_DRIVE: MCU1.12 (D2_PWM); also elsewhere on the board
SW_BOOST: L1.2, U2.5 (SW)
TEMP_SENSE: MCU1.13 (D1_TEMP), R7.2, TH1.1
VBAT: C1.1, D1.1 (K), J1.1, J2.1, L1.1, Q2.1 (S), Q2.2 (S), Q2.3 (S), R3.1, U2.2 (EN), U2.3 (VIN)
VBAT_SENSE: MCU1.14 (D0_VBAT), R3.2, R4.1
XIAO_5V: D2.1 (K), MCU1.1 (5V)

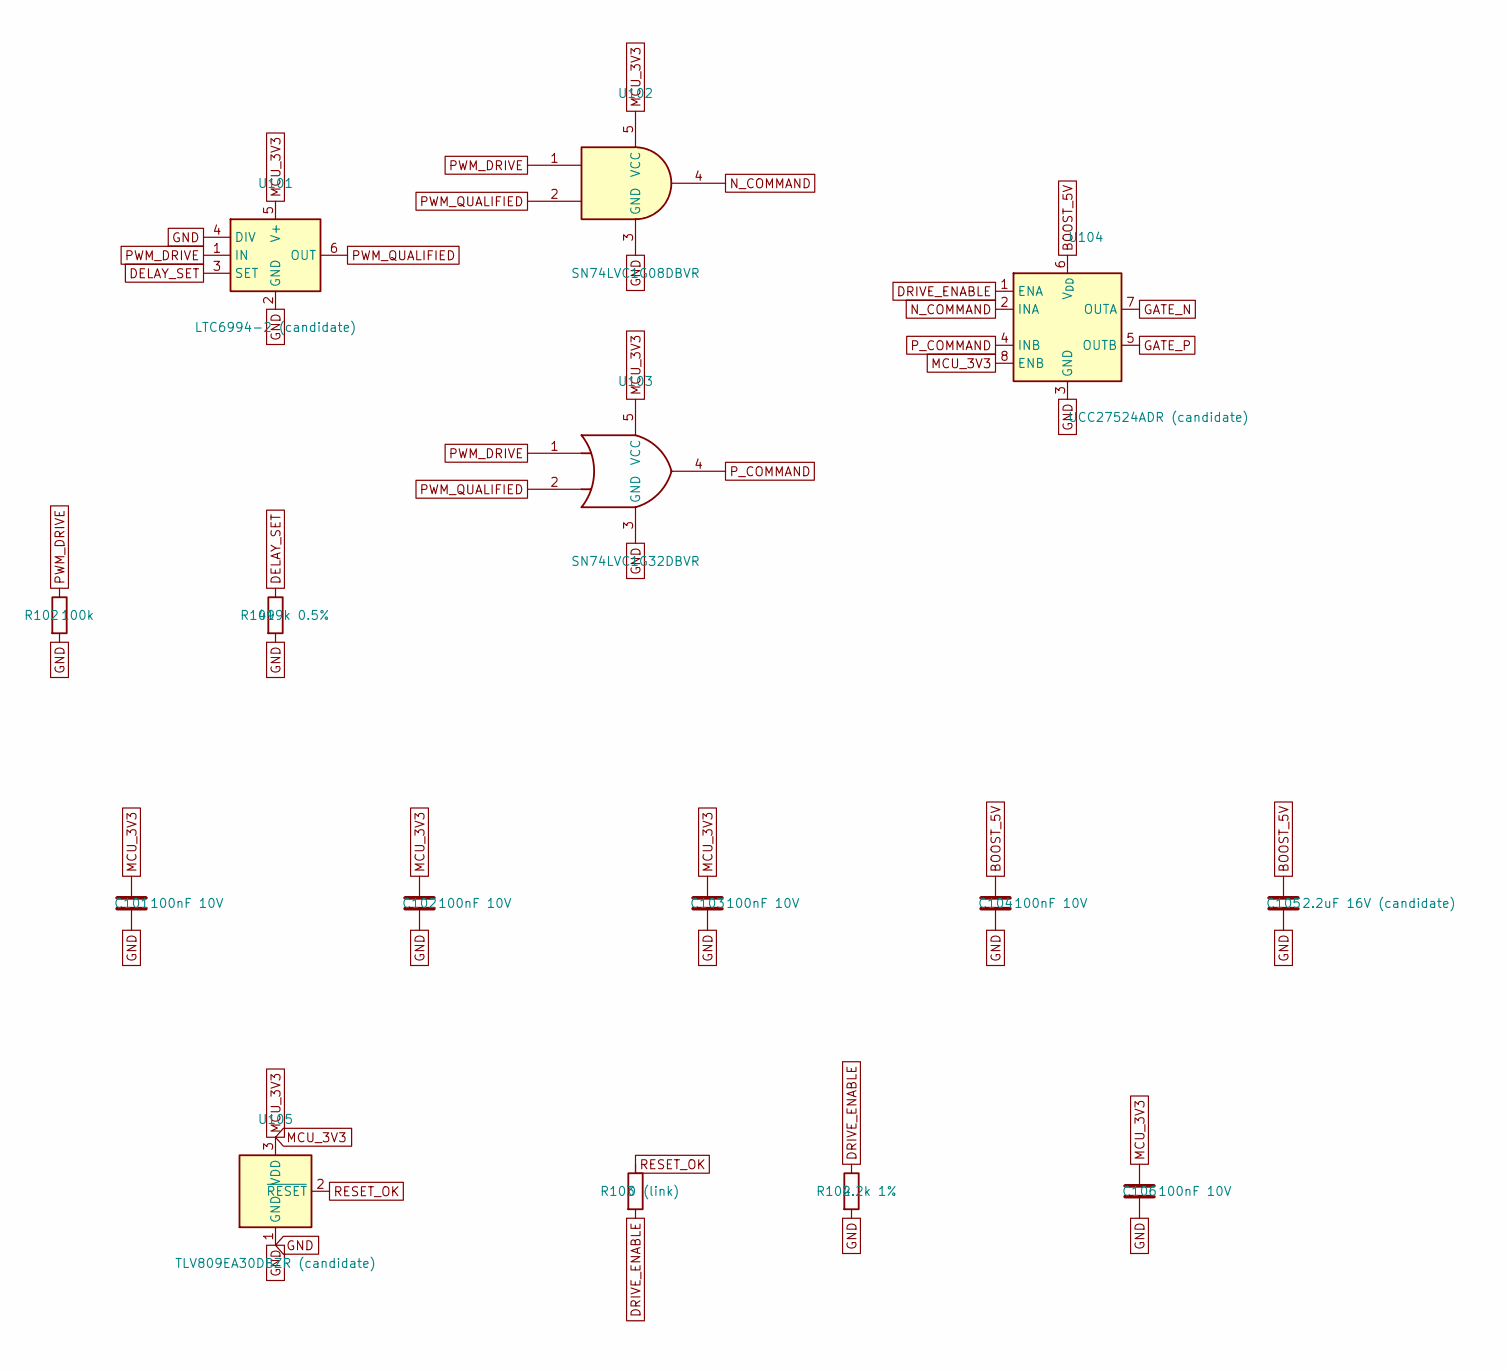
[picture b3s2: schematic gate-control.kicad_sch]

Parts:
C101, C102, C103, C104, C106: 100nF 10V; C_0402_1005Metric
C105: 2.2uF 16V (candidate); C_0603_1608Metric
R101: 499k 0.5%; R_0603_1608Metric
R102: 100k; R_0402_1005Metric
R103: 0 (link); R_0402_1005Metric
R104: 2.2k 1%; R_0402_1005Metric
U101: LTC6994-2 (candidate); TSOT-23-6; MPN LTC6994IS6-2#TRMPBF
U102: SN74LVC1G08DBVR; SOT-23-5; MPN SN74LVC1G08DBVR
U103: SN74LVC1G32DBVR; SOT-23-5; MPN SN74LVC1G32DBVR
U104: UCC27524ADR (candidate); SOIC-8_3.9x4.9mm_P1.27mm; MPN UCC27524ADR
U105: TLV809EA30DBZR (candidate); SOT-23; MPN TLV809EA30DBZR

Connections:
BOOST_5V: C104.1, C105.1, U104.6 (V_{DD}); also elsewhere on the board
DELAY_SET: R101.1, U101.3 (SET)
DRIVE_ENABLE: R103.2, R104.1, U104.1 (ENA)
GATE_N: U104.7 (OUTA); also elsewhere on the board
GATE_P: U104.5 (OUTB); also elsewhere on the board
GND: C101.2, C102.2, C103.2, C104.2, C105.2, C106.2, R101.2, R102.2, R104.2, U101.2 (GND), U101.4 (DIV), U102.3 (GND), U103.3 (GND), U104.3 (GND), U105.1 (GND); also elsewhere on the board
MCU_3V3: C101.1, C102.1, C103.1, C106.1, U101.5 (V+), U102.5 (VCC), U103.5 (VCC), U104.8 (ENB), U105.3 (VDD); also elsewhere on the board
N_COMMAND: U102.4, U104.2 (INA)
PWM_DRIVE: R102.1, U101.1 (IN), U102.1, U103.1; also elsewhere on the board
PWM_QUALIFIED: U101.6 (OUT), U102.2, U103.2
P_COMMAND: U103.4, U104.4 (INB)
RESET_OK: R103.1, U105.2 (~RESET)
